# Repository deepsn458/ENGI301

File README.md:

# ENGI301
This is a repository for my ENGI301 (Introduction to Practical Electrical Engineering) coursework

The main project is a two-player pattern guesser game made using the Pocket Beagle microprocessor.

[project_01](https://github.com/deepsn458/ENGI301/tree/main/project_01) contains the python code used to run the game

[project_02](https://github.com/deepsn458/ENGI301/tree/main/project_02) contains the schematics and board files for the PCB that was designed for the game

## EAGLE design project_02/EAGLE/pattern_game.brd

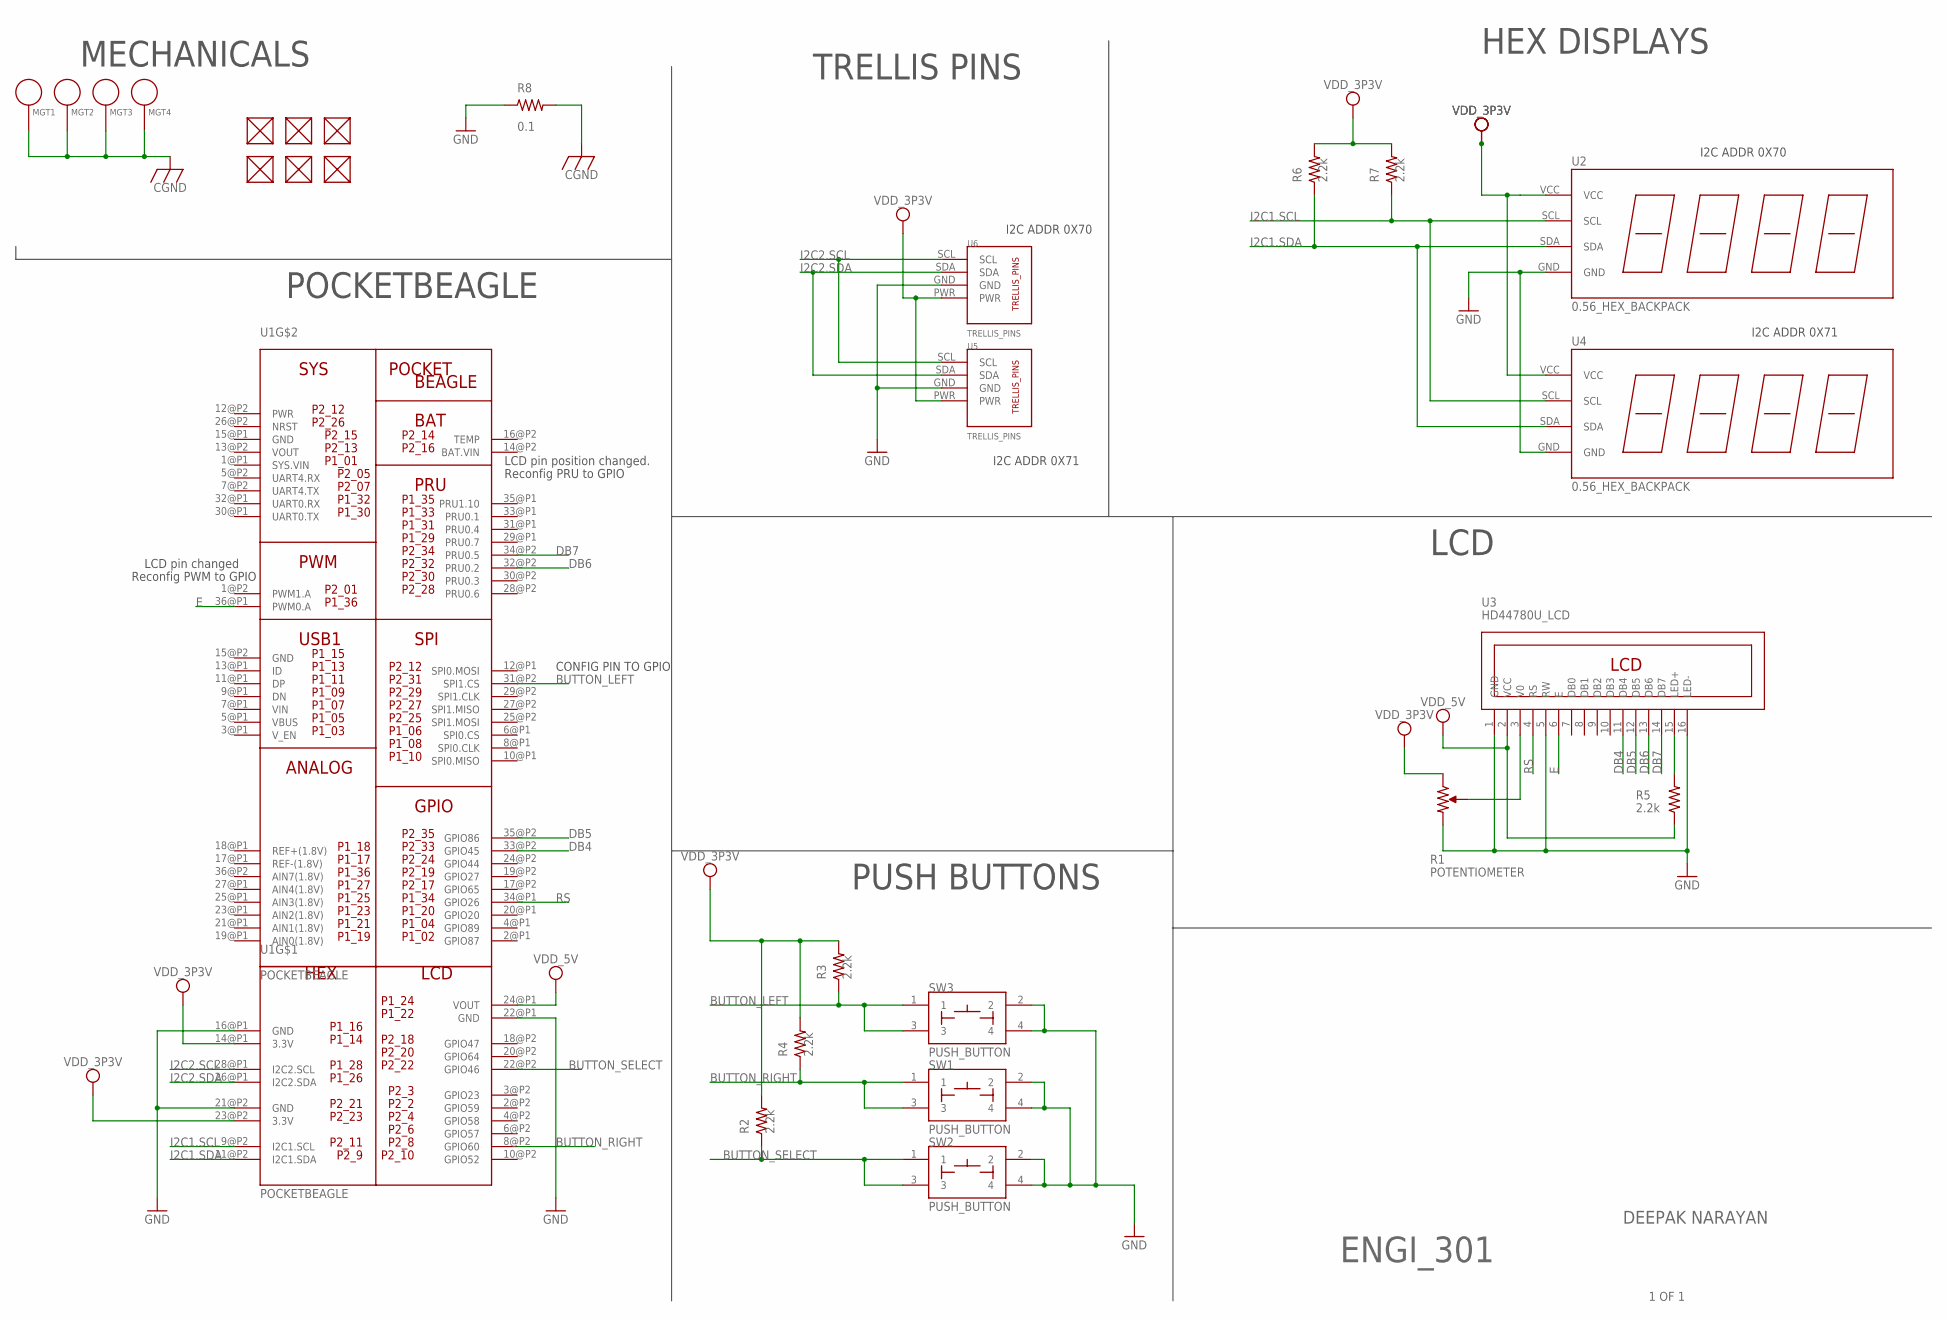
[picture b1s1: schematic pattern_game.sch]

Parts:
FUD1, FUD2, FUD3, FUD4, FUD5, FUD6: FIDUCIAL; FIDUCIAL_40MIL
MGT1, MGT2, MGT3, MGT4: MOUNTING_HOLE
R1: POTENTIOMETER; POT-PO90S
R2, R3, R4, R5, R6, R7: 2.2k; R0603
R8: 0.1; R0603
SW1, SW2, SW3: PUSH_BUTTON; BUTTON_12.5MM
U1: POCKETBEAGLE
U2, U4: 0.56_HEX_BACKPACK
U3: HD44780U_LCD
U5, U6: TRELLIS_PINS

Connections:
BUTTON_LEFT: R3.1, SW3.1, SW3.3, U1.31@P2 (SPI1.CS)
BUTTON_RIGHT: R4.1, SW1.1, SW1.3, U1.8@P2 (GPIO60)
BUTTON_SELECT: R2.1, SW2.1, SW2.3, U1.22@P2 (GPIO46)
CGND: MGT1.P$1, MGT2.P$1, MGT3.P$1, MGT4.P$1, R8.2
DB4: U1.33@P2 (GPIO45), U3.11 (DB4)
DB5: U1.35@P2 (GPIO86), U3.12 (DB5)
DB6: U1.32@P2 (PRU0.2), U3.13 (DB6)
DB7: U1.34@P2 (PRU0.5), U3.14 (DB7)
E: U1.36@P1 (PWM0.A), U3.6 (E)
GND: R1.CW, R8.1, SW1.2, SW1.4, SW2.2, SW2.4, SW3.2, SW3.4, U1.16@P1 (GND), U1.21@P2 (GND), U1.22@P1 (GND), U2.GND, U3.1 (GND), U3.5 (RW), U3.16 (LED-), U4.GND, U5.GND, U6.GND
I2C1.SCL: R7.1, U1.9@P2 (I2C1.SCL), U2.SCL, U4.SCL
I2C1.SDA: R6.1, U1.11@P2 (I2C1.SDA), U2.SDA, U4.SDA
I2C2.SCL: U1.28@P1 (I2C2.SCL), U5.SCL, U6.SCL
I2C2.SDA: U1.26@P1 (I2C2.SDA), U5.SDA, U6.SDA
unnamed: R1.S, U3.3 (V0)
unnamed: R5.2, U3.15 (LED+)
RS: U1.34@P1 (GPIO26), U3.4 (RS)
VDD_3P3V: R1.CCW, R2.2, R3.2, R4.2, R6.2, R7.2, U1.14@P1 (3.3V), U1.23@P2 (3.3V), U2.VCC, U4.VCC, U5.PWR, U6.PWR
VDD_5V: R5.1, U1.24@P1 (VOUT), U3.2 (VCC)

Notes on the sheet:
LCD
HEX DISPLAYS
I2C ADDR 0X70
I2C ADDR 0X71
TRELLIS PINS
POCKETBEAGLE
PUSH BUTTONS
MECHANICALS
ENGI_301
DEEPAK NARAYAN
1 OF 1
LCD pin position changed.
Reconfig PRU to GPIO
LCD pin changed
Reconfig PWM to GPIO
CONFIG PIN TO GPIO

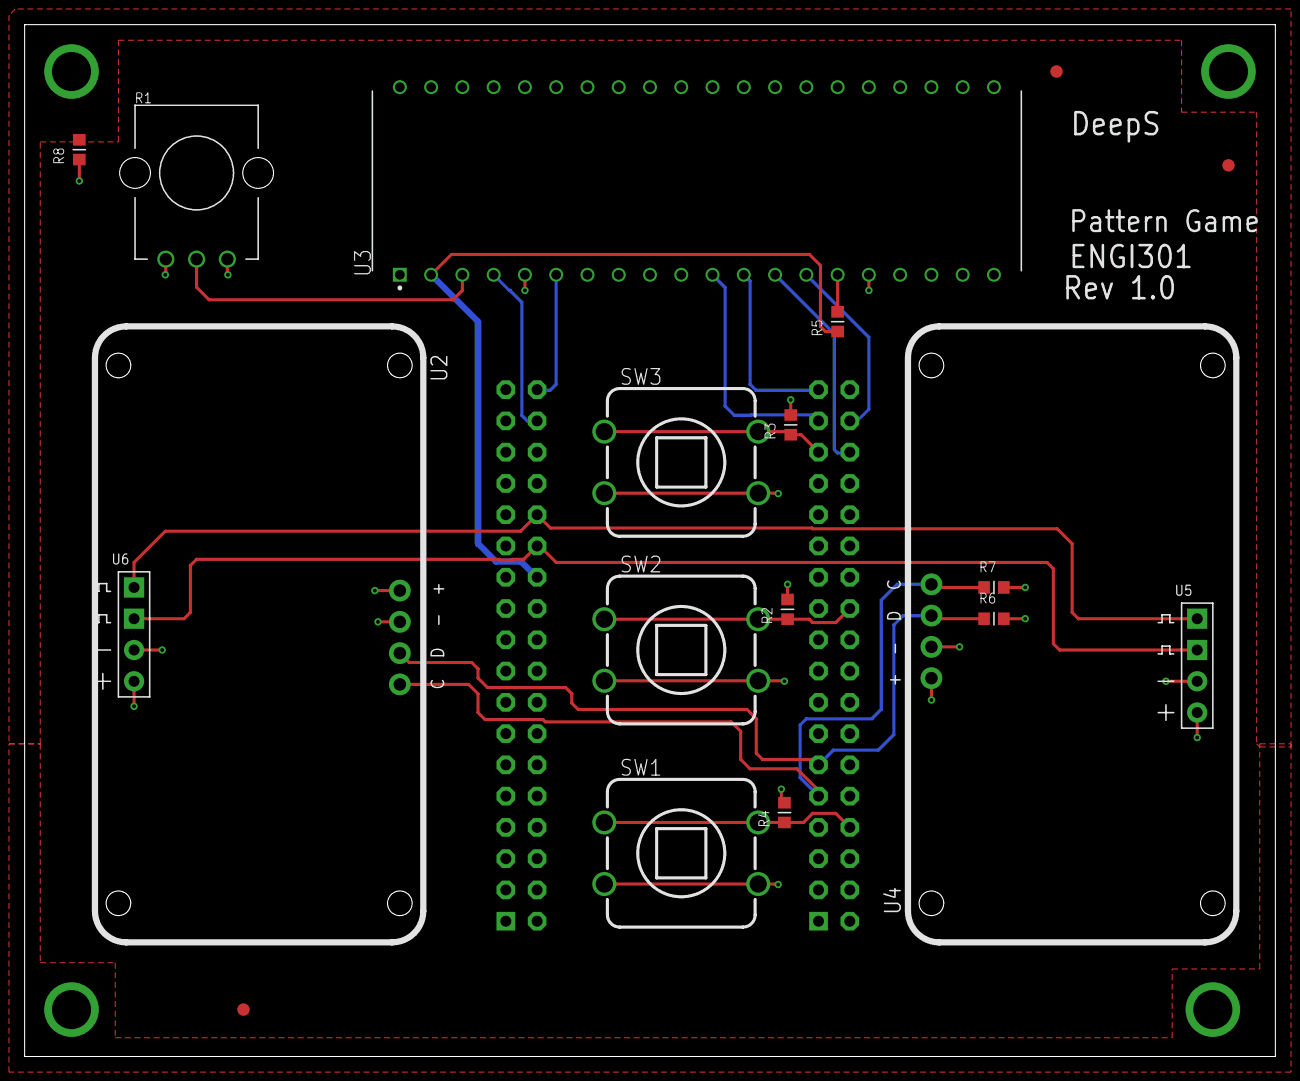
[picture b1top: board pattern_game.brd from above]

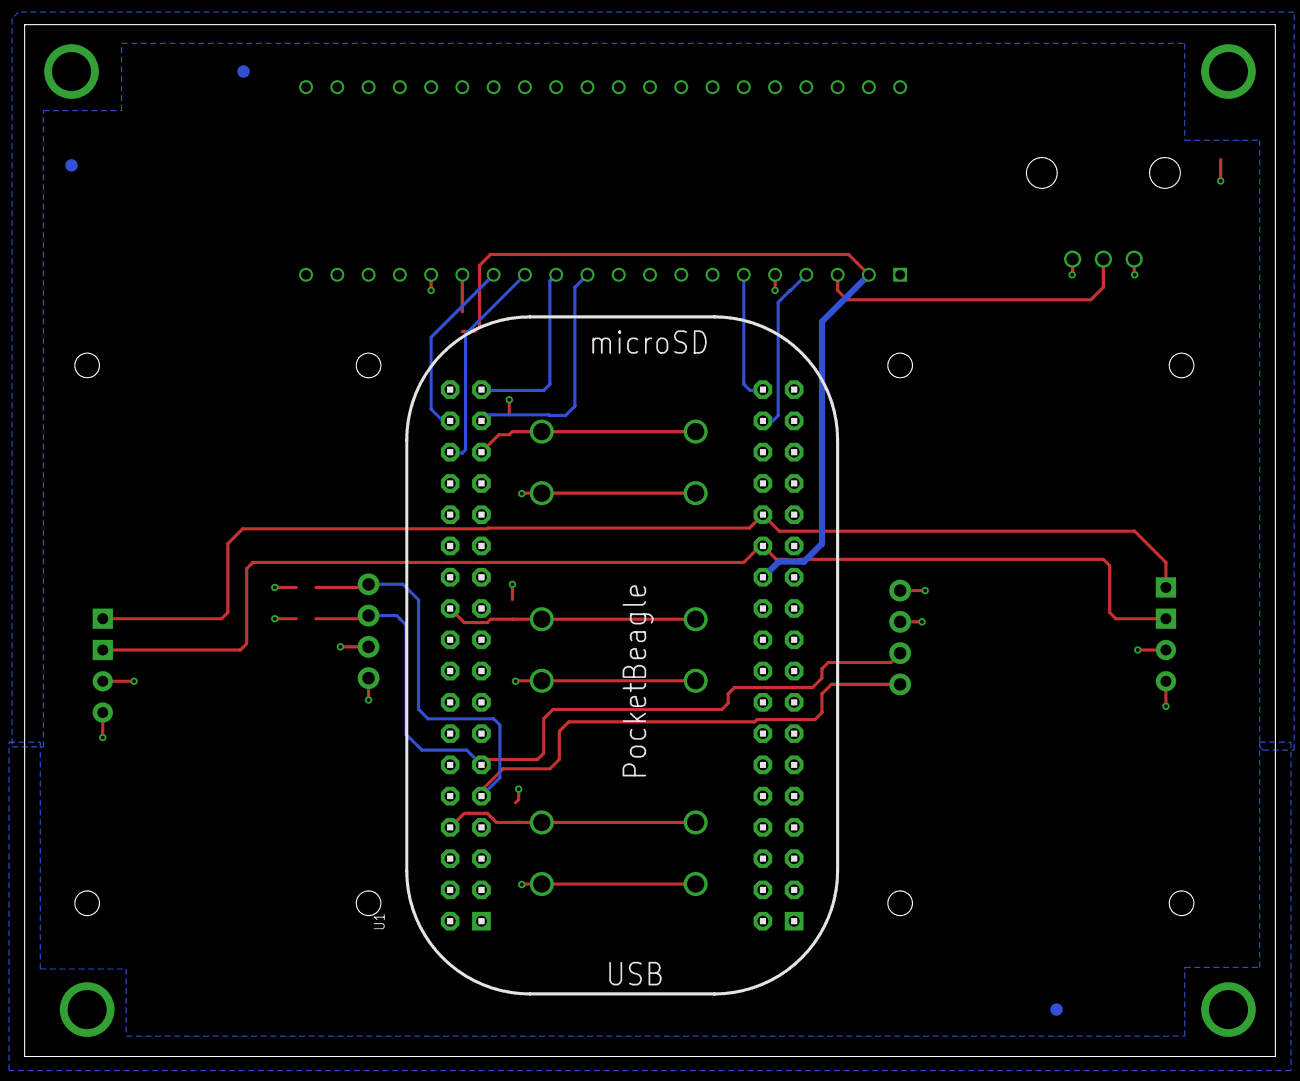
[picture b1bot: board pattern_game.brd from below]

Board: 4 copper layers, 101.6 x 83.8 mm, 27 parts (4 on the bottom side), 19 nets.

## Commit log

2023-01-29 Updating README.md
2023-02-12 Homework #4
2023-02-12 Completed Assignment #03 and Assignment #04
2023-02-14 added project_01
2023-02-14 Added presentation
2023-02-14 updated presentation
2023-02-20 Updated Bill of Materials
2023-02-20 Updated parts list
2023-03-07 adding software block diagram
2023-03-13 hardware driver for trellis
2023-03-13 added some of the skeleton code for the classes
2023-03-21 Added classes
2023-03-28 added drivers
2023-03-28 finished one player setup
2023-04-02 Finished code for onePlayer and twoPlayer
2023-04-02 cleaned up drivers
2023-04-02 Auto boot code added
2023-04-03 final edits
2023-04-04 Added the documentation
2023-04-24 Added library
2023-05-02 added lbr sch and brd files
2023-05-02 addded other documentation
2023-05-02 Rename PATTERN_GAME.lbr to patten_game.lbr
2023-05-02 added pdfs of schematic and board
